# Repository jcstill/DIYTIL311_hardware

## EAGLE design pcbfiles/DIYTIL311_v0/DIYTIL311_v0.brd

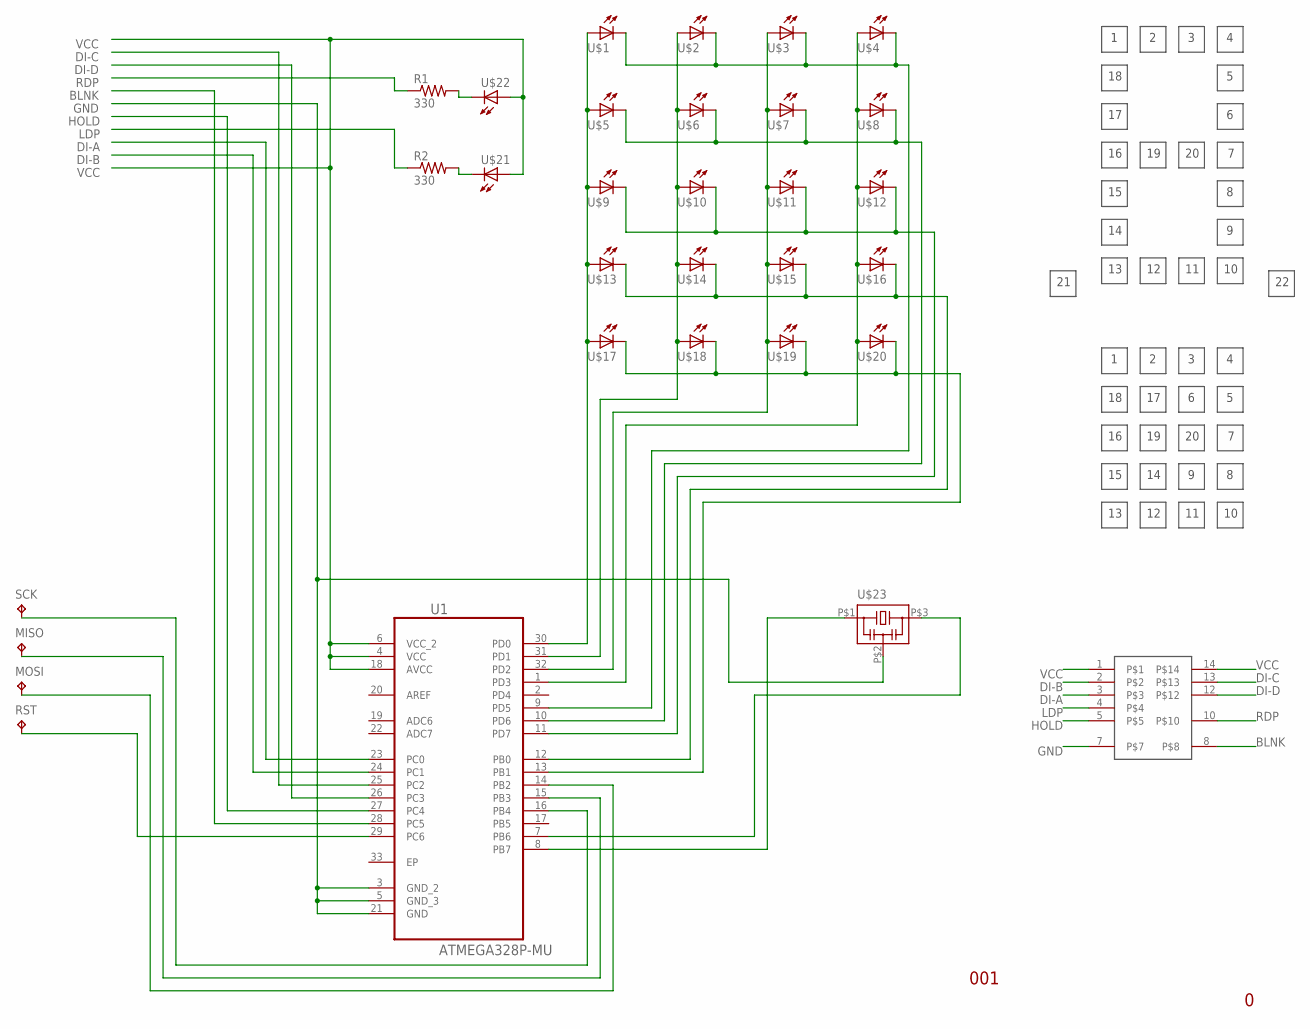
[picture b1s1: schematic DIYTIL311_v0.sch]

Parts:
MISO: TPB1,27; B1,27
MOSI: TPB1,27; B1,27
R1, R2: 330; R0201
RST: TPB1,27; B1,27
SCK: TPB1,27; B1,27
U1: ATMEGA328P-MU; QFN50P500X500X100-33N
U$1, U$2, U$3, U$4, U$5, U$6, U$7, U$8, U$9, U$10, U$11, U$12, U$13, U$14, U$15, U$16, U$17, U$18, U$19, U$20, U$21, U$22: 0201.LED0201; LEDC0603X33
U$23: CSTNE16M0V53Z000R0; MFF
U$24: TIL311DIP; TIL311DIP_FOOTPRINT

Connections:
BLNK: U1.28 (PC5), U$24.8
DI-A: U1.23 (PC0), U$24.3
DI-B: U1.24 (PC1), U$24.2
DI-C: U1.25 (PC2), U$24.13
DI-D: U1.26 (PC3), U$24.12
GND: U1.3 (GND_2), U1.5 (GND_3), U1.21 (GND), U$23.P$2 (2), U$24.7
HOLD: U1.27 (PC4), U$24.5
LDP: R2.1, U$24.4
unnamed: R1.2, U$22.2 (C)
unnamed: R2.2, U$21.2 (C)
unnamed: U1.30 (PD0), U$1.1 (A), U$5.1 (A), U$9.1 (A), U$13.1 (A), U$17.1 (A)
unnamed: U1.31 (PD1), U$2.1 (A), U$6.1 (A), U$10.1 (A), U$14.1 (A), U$18.1 (A)
unnamed: U1.32 (PD2), U$3.1 (A), U$7.1 (A), U$11.1 (A), U$15.1 (A), U$19.1 (A)
unnamed: U1.1 (PD3), U$4.1 (A), U$8.1 (A), U$12.1 (A), U$16.1 (A), U$20.1 (A)
unnamed: U1.9 (PD5), U$1.2 (C), U$2.2 (C), U$3.2 (C), U$4.2 (C)
unnamed: U1.10 (PD6), U$5.2 (C), U$6.2 (C), U$7.2 (C), U$8.2 (C)
unnamed: U1.11 (PD7), U$9.2 (C), U$10.2 (C), U$11.2 (C), U$12.2 (C)
unnamed: U1.12 (PB0), U$13.2 (C), U$14.2 (C), U$15.2 (C), U$16.2 (C)
unnamed: U1.13 (PB1), U$17.2 (C), U$18.2 (C), U$19.2 (C), U$20.2 (C)
unnamed: SCK.TP, U1.16 (PB4)
unnamed: MISO.TP, U1.15 (PB3)
unnamed: MOSI.TP, U1.14 (PB2)
unnamed: RST.TP, U1.29 (PC6)
unnamed: U1.7 (PB6), U$23.P$3 (3)
unnamed: U1.8 (PB7), U$23.P$1 (1)
RDP: R1.1, U$24.10
VCC: U1.4 (VCC), U1.6 (VCC_2), U1.18 (AVCC), U$21.1 (A), U$22.1 (A), U$24.1, U$24.14

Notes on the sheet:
001

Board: 2 copper layers, 31 parts (5 on the bottom side), 27 nets, no tracks yet.

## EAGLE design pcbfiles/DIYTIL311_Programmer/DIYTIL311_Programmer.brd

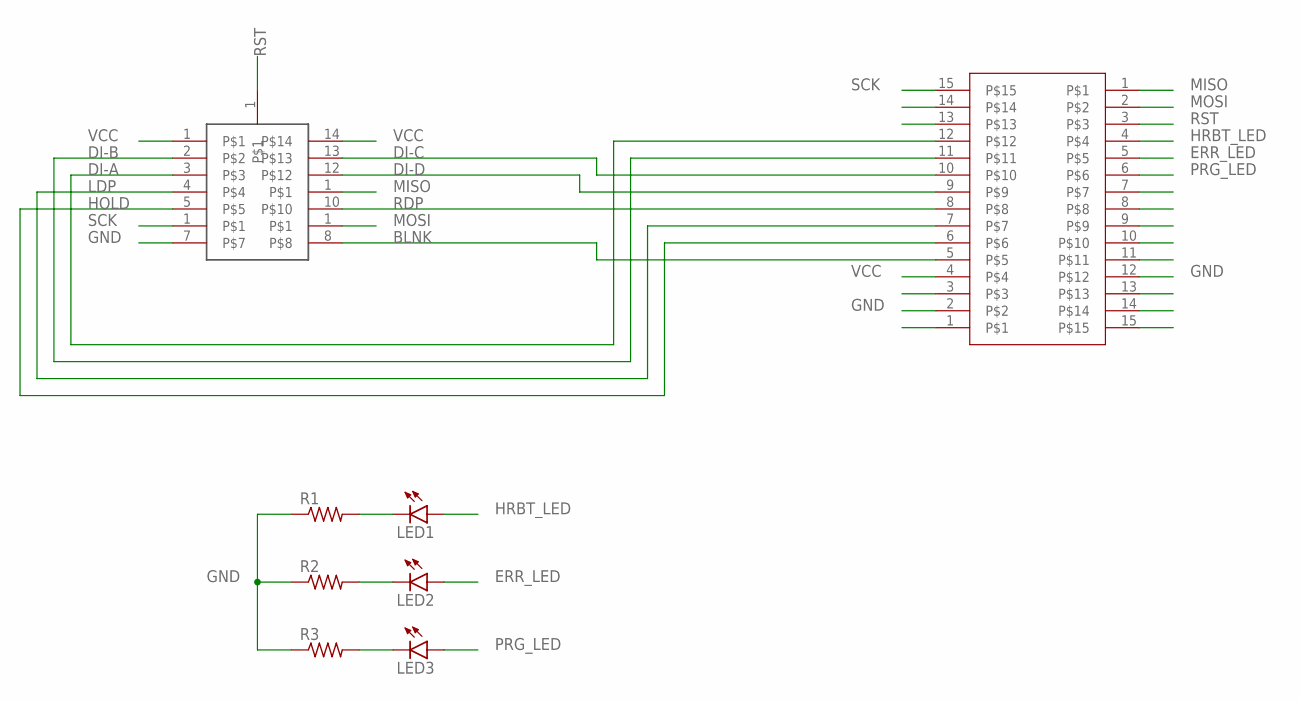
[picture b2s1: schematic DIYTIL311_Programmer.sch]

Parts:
LED1, LED2, LED3: LED5MM
MISO: 1X1_2.54MM1X1; 1X1_2.54MM_FOOTPRINT
MOSI: 1X1_2.54MM1X1; 1X1_2.54MM_FOOTPRINT
R1, R2, R3: R-US_0204/7; 0204/7
RST: 1X1_2.54MM1X1; 1X1_2.54MM_FOOTPRINT
SCK: 1X1_2.54MM1X1; 1X1_2.54MM_FOOTPRINT
U$1: TIL311DIP; TIL311DIP_FOOTPRINT
U$2, U$3: 1X15_2.54MM1X15_2.54MM; 1X15_2.54MM_FOOTPRINT

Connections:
BLNK: U$1.8, U$2.5
DI-A: U$1.3, U$2.12
DI-B: U$1.2, U$2.11
DI-C: U$1.13, U$2.10
DI-D: U$1.12, U$2.9
ERR_LED: LED2.A, U$3.5
GND: R1.1, R2.1, R3.1, U$1.7, U$2.2, U$3.12
HOLD: U$1.5, U$2.6
HRBT_LED: LED1.A, U$3.4
LDP: U$1.4, U$2.7
MISO: MISO.1, U$3.1
MOSI: MOSI.1, U$3.2
unnamed: LED1.K (C), R1.2
unnamed: LED2.K (C), R2.2
unnamed: LED3.K (C), R3.2
PRG_LED: LED3.A, U$3.6
RDP: U$1.10, U$2.8
RST: RST.1, U$3.3
SCK: SCK.1, U$2.15
VCC: U$1.1, U$1.14, U$2.4

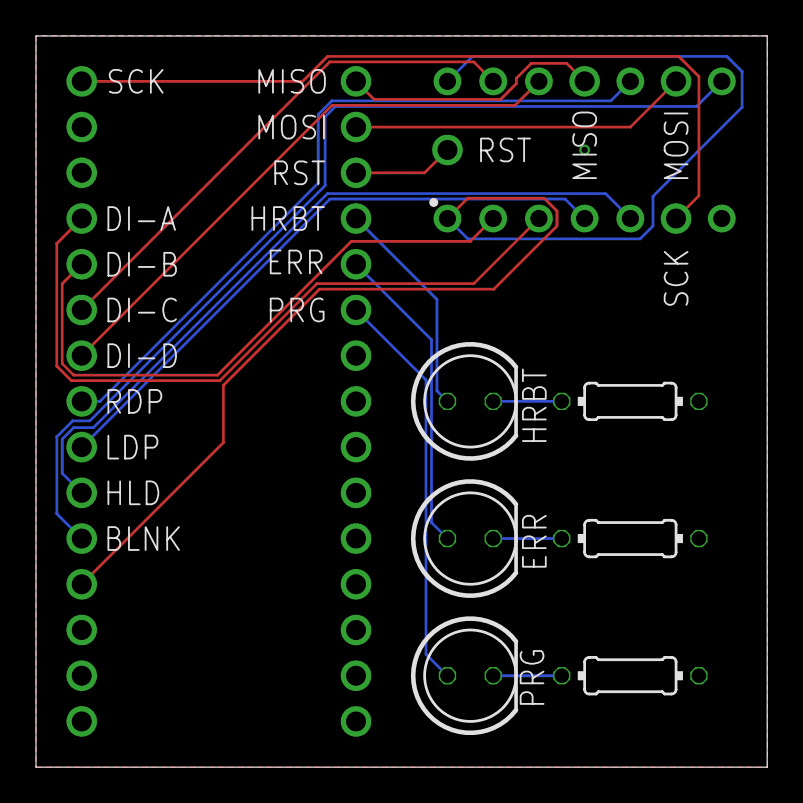
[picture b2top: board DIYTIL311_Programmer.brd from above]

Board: 2 copper layers, 40.6 x 40.6 mm, 13 parts (0 on the bottom side), 20 nets.

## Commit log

2020-02-25 Add misc files
2020-02-25 Consolidating Repos
2021-04-13 Add sensitive data to .gitignore
2021-04-18 remove more sensitive data
